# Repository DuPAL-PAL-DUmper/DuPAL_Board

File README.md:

# DuPAL board

## DISCLAIMER

Any use of this project is **under your own responsibility**.
You will be responsible of checking the correct construction and functionality of your board and the compatiblity of the chips You will insert into it.
By using this project You will agree that I cannot be held responsible if it will destroy any of your devices, damage your computer, burn down your house or whatever.

**Do NOT come to me for hand-holding** using this. It is NOT a plug-and-play tool, and it is something I created **for my own use** and I released in case someone might have an use for it.

## Introduction

The DuPAL boards are tools meant to help in dumping/reversing the content of some PLDs and memories.

The original DuPAL revision 2, currently supported by most tools, but limited in support to PAL devices (with the exclusion of PAL22) can be found [here](https://github.com/DuPAL-PAL-DUmper/DuPAL_Board/tree/master/board/DuPal_DIP).

The [DuPAL V3](https://github.com/DuPAL-PAL-DUmper/DuPAL_Board/tree/master/board/DuPal_V3), AKA "dupico", has more potential and will eventually support a much larger number of devices, but most of the tools have not yet been ported to it. Adapter pods for the dupico can be found [here](https://github.com/DuPAL-PAL-DUmper/DuPAL_Board/tree/master/board/dupico_pods).

### Sponsorship

This project is kindly sponsored by [PCBWay](https://pcbway.com).
PCBWay specializes in manufacturing high-quality PCBs and makes them affordable to hobbyist and professionals alike.

The range of services they offer include PCB prototyping, assembly, instant quotes for your order, a verification process by a team
of experts and an easy to use, hassle-free order process.

I'm grateful to PCBWay for the support in creating this project.

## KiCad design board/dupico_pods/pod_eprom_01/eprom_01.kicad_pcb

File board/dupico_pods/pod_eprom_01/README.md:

# EPROM_01 POD for dupico

## DISCLAIMER

Any use of this project is **under your own responsibility**.
You will be responsible of checking the correct construction and functionality of your board and the compatiblity of the chips You will insert into it.
By using this project You will agree that I cannot be held responsible if it will destroy any of your devices, damage your computer, burn down your house or whatever.

**Do NOT come to me for hand-holding** using this. It is NOT a plug-and-play tool, and it is something I created **for my own use** and I released in case someone might have an use for it.

## Introduction

The EPROM_01 POD is an adapter for the DuPAL V3 (AKA "dupico") meant to support the most common 24/28/32 pin ROMs, the only requirement being that they can be powered by 5V, have GND in the lower left pin and VCC in the upper right.

### Usage

This device is inserted in the ZIF socket of the dupico: if you installed a ZIF42 socket, it will fill all the 42 pins, if you installed a 48 pin socket, make sure to leave the bottom 6 pins empty (fit this in the topmost part of the socket).

When you fit a ROM device in it, make sure to align it to the bottom of the pod socket (so, a 28 pin device will leave empty the topmost 4 pins in the socket). 

Pin 32 on the pod socket is **hardwired to VCC**, there are other 7 selectable pins that can provide power, configured with 3 pins on the **ZIF42** socket:

| 24 | 23 | 22 | -> | Powered Pin (32 pin socket) |
| -- | -- | -- | -- | --------------------------- |
|  0 |  0 |  0 |    | 30 / 32                     |
|  0 |  0 |  1 |    | 28 / 32                     |
|  0 |  1 |  0 |    | 26 / 32                     |
|  0 |  1 |  1 |    | 25 / 32                     |
|  1 |  0 |  0 |    | 24 / 32                     |
|  1 |  0 |  1 |    | 23 / 32                     |
|  1 |  1 |  0 |    | 20 / 32                     |
|  1 |  1 |  1 |    | 32 only                     |

#### Socket connections

This drawing shows how the pin on the 32 socket are wired to the pins on the dupico's ZIF42.

```
            __ __
   1 ---> 1   U  32 <--- +5V (fixed)
   2 ---> 2      31 <-- 41
   3 ---> 3      30 <-- 40 --- Selectable +5V
   4 ---> 4      29 <-- 39
   5 ---> 5      28 <-- 38 --- Selectable +5V
   6 ---> 6      27 <-- 37
   7 ---> 7      26 <-- 36 --- Selectable +5V
   8 ---> 8      25 <-- 35 --- Selectable +5V
   9 ---> 9      24 <-- 34 --- Selectable +5V
  10 --> 10      23 <-- 33 --- Selectable +5V
  11 --> 11      22 <-- 32
  12 --->12      21 <-- 31
  13 --> 13      20 <-- 30 --- Selectable +5V
  14 --> 14      19 <-- 29
  15 --->15      18 <-- 28
GND ---> 16______17 <-- 27

```

## Hardware

The board was designed with [KiCad](https://kicad.org/) EDA.

In its current form, the board is relatively simple build, using through-hole and (non fine pitched) SMD components.

You can order the PCBs at [PCBWay](https://www.pcbway.com/project/shareproject/dupico_EPROM_01_POD_ed82b51c.html)!

### Bill of Materials

| Component         | Qty | Type / Value                   | Notes                                                                                            |
| ----------------- | --- | ------------------------------ | ------------------------------------------------------------------------------------------------ |
| J1                |  2  | 21 pin 2.54mm headers          | Use rounded pin headers to put less stress on dupico ZIF, snip the protruding part of the header |
| C1, C2            |  2  | 100nF / 1206 / ceramic         |                                                                                                  |
| Q1 - Q7           |  7  | MMBT3906                       |                                                                                                  |
| J2                |  1  | 32 pin wide socket             | Solder this AFTER the two J1 headers, you can use a ZIF32 socket.                                |
| U2                |  1  | 74ACT138 SOIC-16               |                                                                                                  |
| R1 - R7           |  7  | 1K / 1206                      |                                                                                                  |

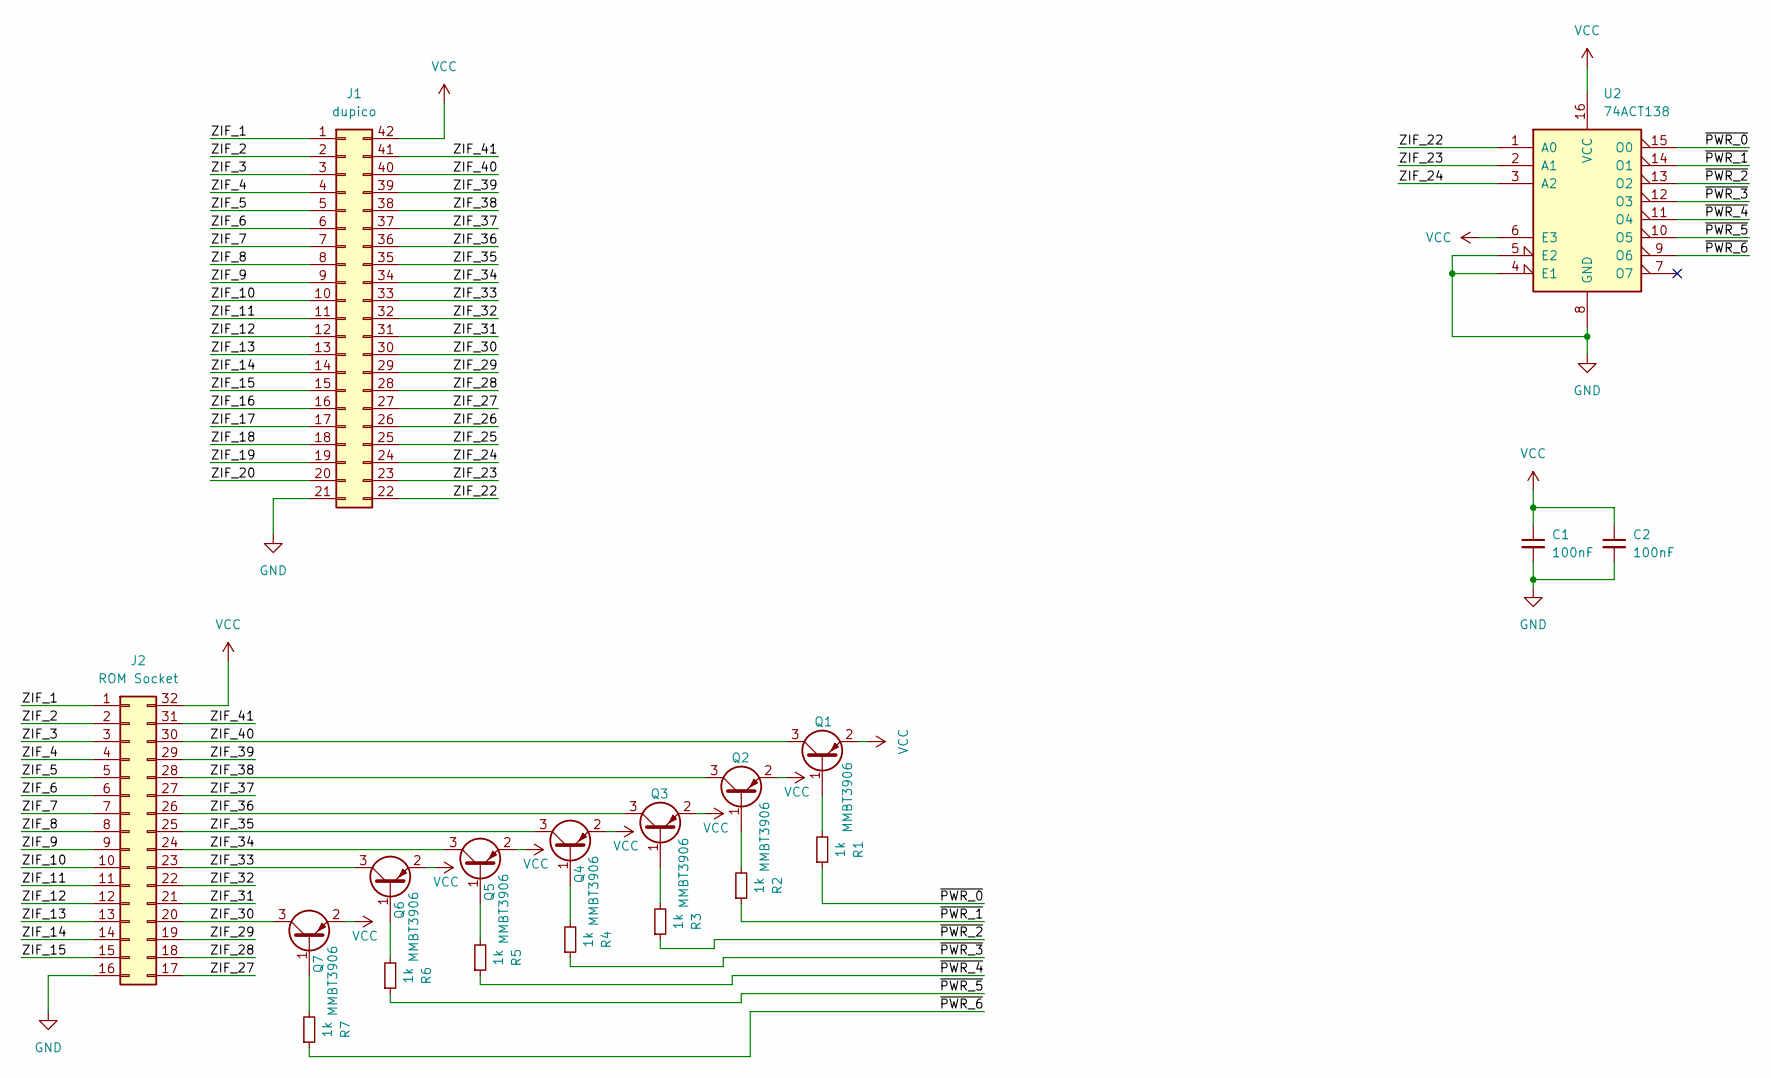
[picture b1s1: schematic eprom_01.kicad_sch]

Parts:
C1, C2: 100nF; C_1206_3216Metric_Pad1.33x1.80mm_HandSolder
J1: dupico; DIP-42_W15.24mm
J2: ROM Socket; DIP_Socket-32_W11.9_W12.7_W15.24_W17.78_W18.5_3M_232-1285-0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
Q1, Q2, Q3, Q4, Q5, Q6, Q7: MMBT3906; SOT-23
R1, R2, R3, R4, R5, R6, R7: 1k; R_1206_3216Metric_Pad1.30x1.75mm_HandSolder
U2: 74ACT138; SOIC-16_3.9x9.9mm_P1.27mm

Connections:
/ZIF_1: J1.1, J2.1
/ZIF_2: J1.2, J2.2
/ZIF_3: J1.3, J2.3
/ZIF_4: J1.4, J2.4
/ZIF_5: J1.5, J2.5
/ZIF_6: J1.6, J2.6
/ZIF_7: J1.7, J2.7
/ZIF_8: J1.8, J2.8
/ZIF_9: J1.9, J2.9
/ZIF_10: J1.10, J2.10
/ZIF_11: J1.11, J2.11
/ZIF_12: J1.12, J2.12
/ZIF_13: J1.13, J2.13
/ZIF_14: J1.14, J2.14
/ZIF_15: J1.15, J2.15
/ZIF_16: J1.16
/ZIF_17: J1.17
/ZIF_18: J1.18
/ZIF_19: J1.19
/ZIF_20: J1.20
/ZIF_22: J1.22, U2.1 (A0)
/ZIF_23: J1.23, U2.2 (A1)
/ZIF_24: J1.24, U2.3 (A2)
/ZIF_25: J1.25
/ZIF_26: J1.26
/ZIF_27: J1.27, J2.17
/ZIF_28: J1.28, J2.18
/ZIF_29: J1.29, J2.19
/ZIF_30: J1.30, J2.20, Q7.3 (C)
/ZIF_31: J1.31, J2.21
/ZIF_32: J1.32, J2.22
/ZIF_33: J1.33, J2.23, Q6.3 (C)
/ZIF_34: J1.34, J2.24, Q5.3 (C)
/ZIF_35: J1.35, J2.25, Q4.3 (C)
/ZIF_36: J1.36, J2.26, Q3.3 (C)
/ZIF_37: J1.37, J2.27
/ZIF_38: J1.38, J2.28, Q2.3 (C)
/ZIF_39: J1.39, J2.29
/ZIF_40: J1.40, J2.30, Q1.3 (C)
/ZIF_41: J1.41, J2.31
/~PWR_0: R1.1, U2.15 (O0)
/~PWR_1: R2.1, U2.14 (O1)
/~PWR_2: R3.1, U2.13 (O2)
/~PWR_3: R4.1, U2.12 (O3)
/~PWR_4: R5.1, U2.11 (O4)
/~PWR_5: R6.1, U2.10 (O5)
/~PWR_6: R7.1, U2.9 (O6)
GND: C1.2, C2.2, J1.21, J2.16, U2.4 (E1), U2.5 (E2), U2.8 (GND)
unnamed: Q1.1 (B), R1.2
unnamed: Q2.1 (B), R2.2
unnamed: Q3.1 (B), R3.2
unnamed: Q4.1 (B), R4.2
unnamed: Q5.1 (B), R5.2
unnamed: Q6.1 (B), R6.2
unnamed: Q7.1 (B), R7.2
VCC: C1.1, C2.1, J1.42, J2.32, Q1.2 (E), Q2.2 (E), Q3.2 (E), Q4.2 (E), Q5.2 (E), Q6.2 (E), Q7.2 (E), U2.6 (E3), U2.16 (VCC)

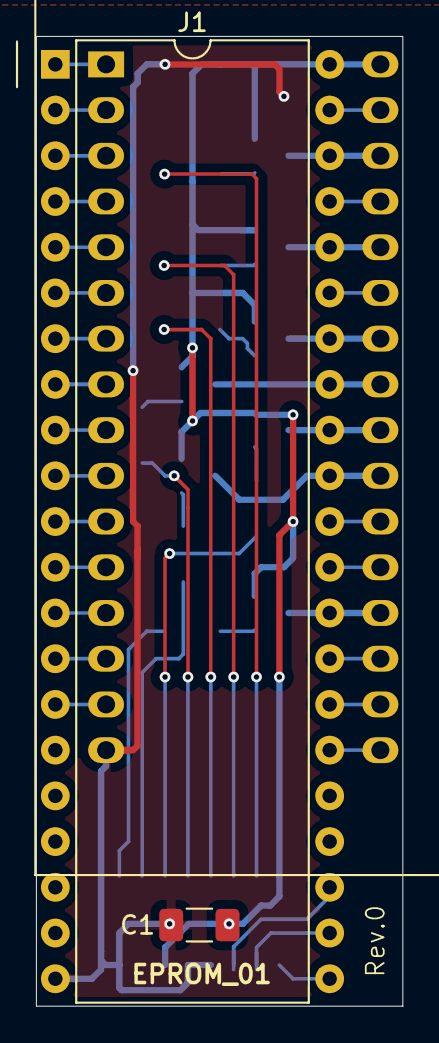
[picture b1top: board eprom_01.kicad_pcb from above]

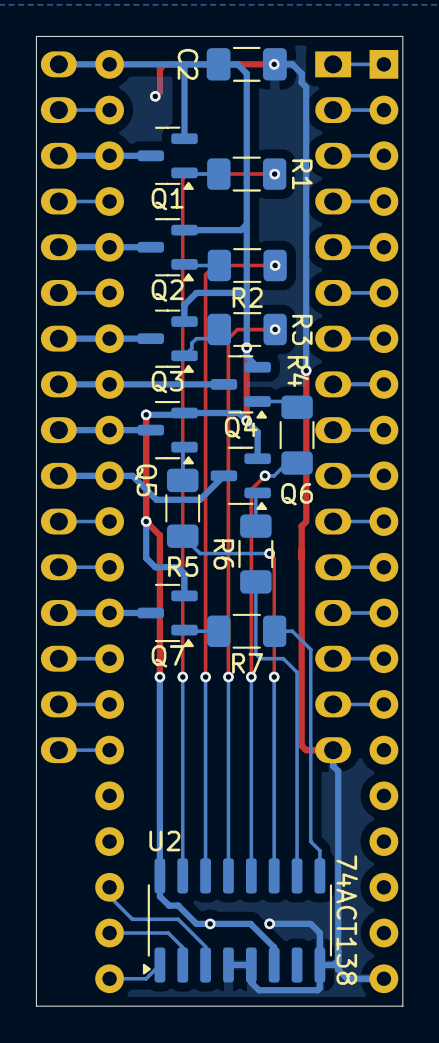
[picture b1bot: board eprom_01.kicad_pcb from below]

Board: 2 copper layers, 20.4 x 53.9 mm, 19 parts (16 on the bottom side), 49 nets.

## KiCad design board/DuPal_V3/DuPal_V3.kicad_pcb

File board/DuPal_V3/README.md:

# DuPAL V3 "dupico" board

## DISCLAIMER

Any use of this project is **under your own responsibility**.
You will be responsible of checking the correct construction and functionality of your board and the compatiblity of the chips You will insert into it.
By using this project You will agree that I cannot be held responsible if it will destroy any of your devices, damage your computer, burn down your house or whatever.

**Do NOT come to me for hand-holding** using this. It is NOT a plug-and-play tool, and it is something I created **for my own use** and I released in case someone might have an use for it.

## Introduction

The DuPAL V3, AKA "dupico" board is a simple circuit that mounts a Raspberry Pico (RP2040), 74HC595 SIPO registers, 74HCT166 PISO registers, and some glue logic and passives.

The board is designed to help me analyze and dump various types of PLDs and memories.

Various adapters (or "pods") can be designed to suit different types of ICs. The pods will be plugged in the ZIF42 socket.

## Software

### Firmware

See [here](https://github.com/DuPAL-PAL-DUmper/dupico_firmware) for details.

### dpdumper

This is a generic dumper for combinatorial ICs. See [here](https://github.com/DuPAL-PAL-DUmper/dpdumper) for the repository.

## Hardware

The board was designed with [KiCad](https://kicad.org/) EDA.

In its current form, the board is relatively simple build, using through-hole and (non fine pitched) SMD components.

### Bill of Materials

| Component         | Qty | Type / Value                   | Notes                                                    |
| ----------------- | --- | ------------------------------ | -------------------------------------------------------- |
| C1, C3 - C14      | 13  | 100nF / 1206 / ceramic         |                                                          |
| C2                |  1  | 10uF / 10V / 1206 / ceramic    |                                                          |
| D1                |  1  | 1N5818                         |                                                          |
| D2, D3, D4        |  3  | Your choice of 1206 SMD LEDs   |                                                          |
| F1                |  1  | 1206 500mA fuse                | https://www.mouser.it/ProductDetail/530-C1F500           |
| J1                |  1  | ZIF42 or ZIF48 socket, wide    | If using ZIF42, leave the bottom 6 pins empty on the PCB |
| J2                |  1  | 1x3 header, 2.54mm pitch       |                                                          |
| J3                |  1  | 2x8 header, 2.54mm pitch       |                                                          |
| J4, J5            |  2  | 1x21 header, 2.54mm pitch      |                                                          |
| K1                |  1  | Omron G6K-2P-Y-DC5             | https://www.mouser.it/ProductDetail/653-G6K-2P-Y-DC5     |
| Q1                |  1  | 2N3904                         |                                                          |
| R1                |  1  | 2.2K / 1206                    |                                                          |
| R2 - R41, R86     | 41  | 10K / 1206                     |                                                          |
| R42, R46 - R85    | 41  | 470K / 1206                    |                                                          |
| R43 - R45         |  3  | 1.2K / 1206                    |                                                          |
| SW1               |  1  | Switch button 6mm              |                                                          |
| U1                |  1  | Pi Pico                        |                                                          |
| U2 - U6           |  5  | 74HCT595 SOIC-16               | HCT variant is important                                 |
| U7                |  1  | 74HCT02 SOIC-14                | HCT variant is important                                 |
| U8 - U12          |  5  | 74HCT166 SOIC-16               | HCT variant is important                                 |
| U13               |  1  | SN74LV1T125DBV SOT-23-5        | https://www.mouser.it/ProductDetail/595-74LV1T125DBVRG4  |

⚠️**WARNING:**⚠️ Note that U10, on the backside of the PCB, has the opposite orientation in respect to U8, U9, U11 and U12. This is NOT a mistake, trust the silkscreen in this case.

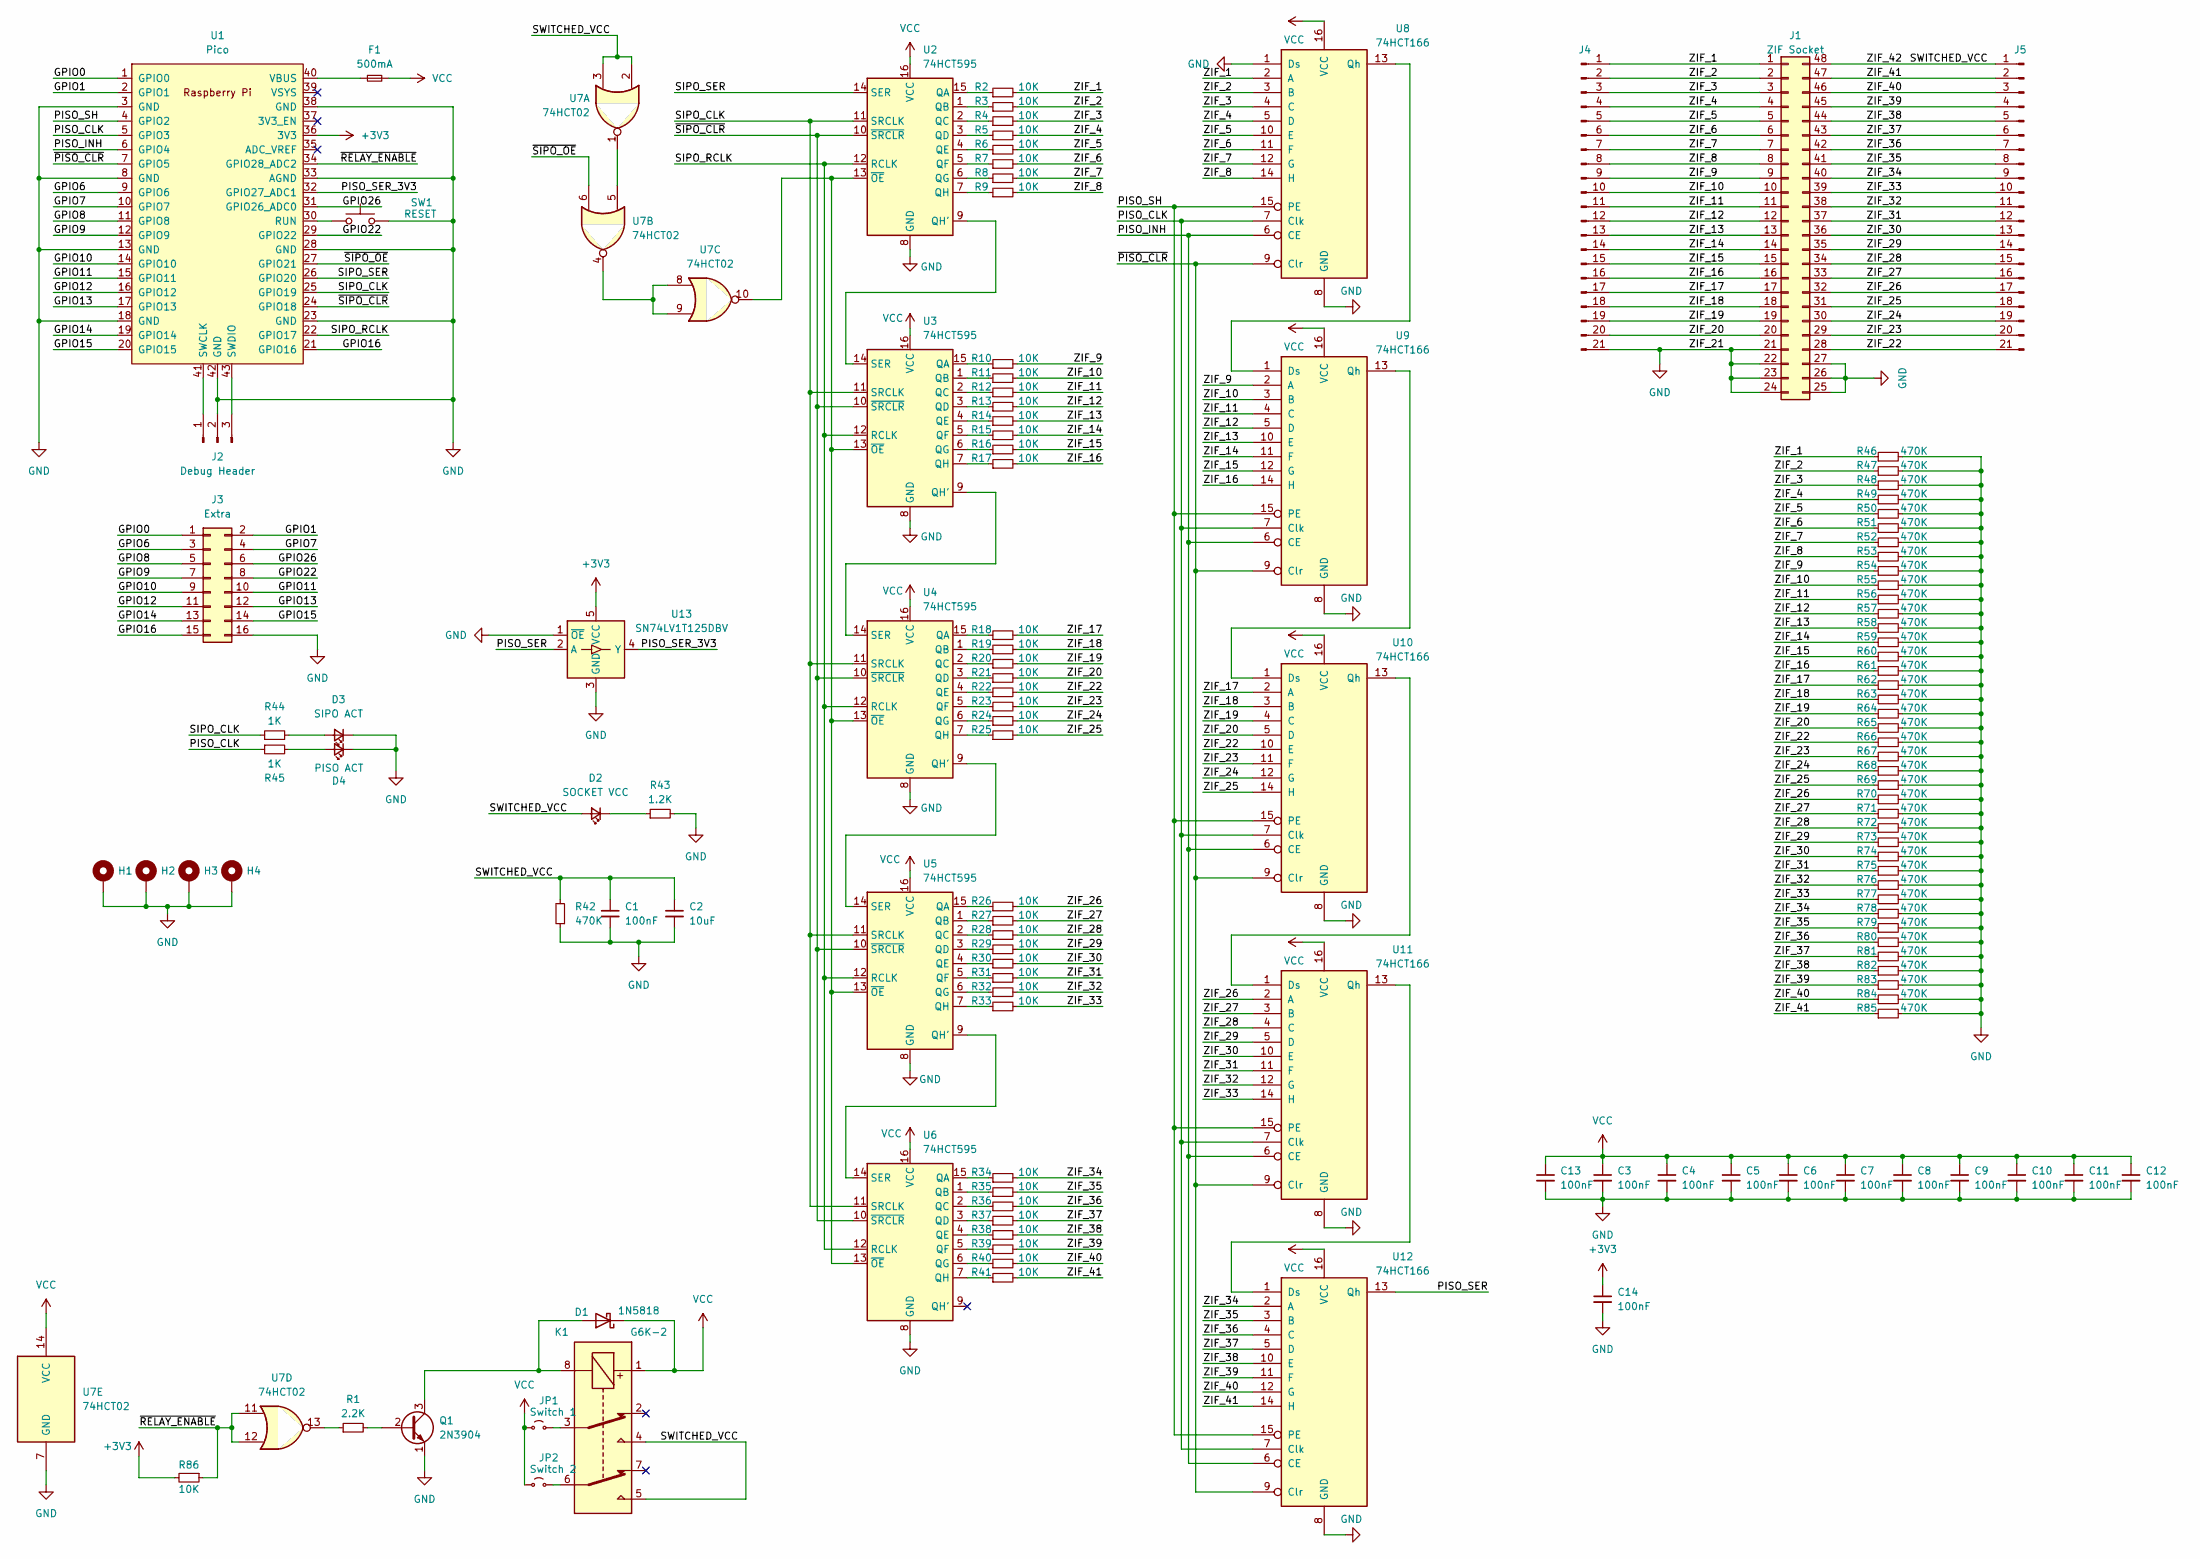
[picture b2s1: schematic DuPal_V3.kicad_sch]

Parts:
C1, C3, C4, C5, C6, C7, C8, C9, C10, C11, C12, C13, C14: 100nF; C_1206_3216Metric_Pad1.33x1.80mm_HandSolder
C2: 10uF; C_1206_3216Metric_Pad1.33x1.80mm_HandSolder
D1: 1N5818; D_DO-41_SOD81_P10.16mm_Horizontal
D2: SOCKET VCC; LED_1206_3216Metric_Pad1.42x1.75mm_HandSolder
D3: SIPO ACT; LED_1206_3216Metric_Pad1.42x1.75mm_HandSolder
D4: PISO ACT; LED_1206_3216Metric_Pad1.42x1.75mm_HandSolder
F1: 500mA; Fuse_1206_3216Metric_Pad1.42x1.75mm_HandSolder
H1, H2, H3, H4: MountingHole_Pad; MountingHole_3.2mm_M3_DIN965_Pad
J1: ZIF Socket; DIP_Socket-48
J2: Debug Header; PinHeader_1x03_P2.54mm_Vertical
J3: Extra; PinHeader_2x08_P2.54mm_Vertical
J4, J5: Conn_01x21_Pin; PinHeader_1x21_P2.54mm_Vertical
JP1: Switch 1; SolderJumper-2_P1.3mm_Bridged_RoundedPad1.0x1.5mm
JP2: Switch 2; SolderJumper-2_P1.3mm_Open_RoundedPad1.0x1.5mm
K1: G6K-2; Relay_DPDT_Omron_G6K-2P-Y
Q1: 2N3904; TO-92_Inline
R1: 2.2K; R_1206_3216Metric_Pad1.30x1.75mm_HandSolder
R2, R3, R4, R5, R6, R7, R8, R9, R10, R11, R12, R13, R14, R15, R16, R17, R18, R19, R20, R21, R22, R23, R24, R25, R26, R27, R28, R29, R30, R31, R32, R33, R34, R35, R36, R37, R38, R39, R40, R41, R86: 10K; R_1206_3216Metric_Pad1.30x1.75mm_HandSolder
R42, R46, R47, R48, R49, R50, R51, R52, R53, R54, R55, R56, R57, R58, R59, R60, R61, R62, R63, R64, R65, R66, R67, R68, R69, R70, R71, R72, R73, R74, R75, R76, R77, R78, R79, R80, R81, R82, R83, R84, R85: 470K; R_1206_3216Metric_Pad1.30x1.75mm_HandSolder
R43: 1.2K; R_1206_3216Metric_Pad1.30x1.75mm_HandSolder
R44, R45: 1K; R_1206_3216Metric_Pad1.30x1.75mm_HandSolder
SW1: RESET; SW_PUSH_6mm
U1: Pico; RPi_Pico_SMD_TH
U2, U3, U4, U5, U6: 74HCT595; SOIC-16_3.9x9.9mm_P1.27mm
U7: 74HCT02; SOIC-14_3.9x8.7mm_P1.27mm
U8, U9, U10, U11, U12: 74HCT166; SOIC-16_3.9x9.9mm_P1.27mm
U13: SN74LV1T125DBV; SOT-23-5

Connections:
+3V3: C14.1, R86.2, U1.36 (3V3), U13.5 (VCC)
/GPIO0: J3.1, U1.1 (GPIO0)
/GPIO1: J3.2, U1.2 (GPIO1)
/GPIO6: J3.3, U1.9 (GPIO6)
/GPIO7: J3.4, U1.10 (GPIO7)
/GPIO8: J3.5, U1.11 (GPIO8)
/GPIO9: J3.7, U1.12 (GPIO9)
/GPIO10: J3.9, U1.14 (GPIO10)
/GPIO11: J3.10, U1.15 (GPIO11)
/GPIO12: J3.11, U1.16 (GPIO12)
/GPIO13: J3.12, U1.17 (GPIO13)
/GPIO14: J3.13, U1.19 (GPIO14)
/GPIO15: J3.14, U1.20 (GPIO15)
/GPIO16: J3.15, U1.21 (GPIO16)
/GPIO22: J3.8, U1.29 (GPIO22)
/GPIO26: J3.6, U1.31 (GPIO26_ADC0)
/PISO_CLK: R45.1, U1.5 (GPIO3), U8.7 (Clk), U9.7 (Clk), U10.7 (Clk), U11.7 (Clk), U12.7 (Clk)
/PISO_INH: U1.6 (GPIO4), U8.6 (CE), U9.6 (CE), U10.6 (CE), U11.6 (CE), U12.6 (CE)
/PISO_SER: U12.13 (Qh), U13.2 (A)
/PISO_SER_3V3: U1.32 (GPIO27_ADC1), U13.4 (Y)
/PISO_SH: U1.4 (GPIO2), U8.15 (PE), U9.15 (PE), U10.15 (PE), U11.15 (PE), U12.15 (PE)
/SIPO_CLK: R44.1, U1.25 (GPIO19), U2.11 (SRCLK), U3.11 (SRCLK), U4.11 (SRCLK), U5.11 (SRCLK), U6.11 (SRCLK)
/SIPO_RCLK: U1.22 (GPIO17), U2.12 (RCLK), U3.12 (RCLK), U4.12 (RCLK), U5.12 (RCLK), U6.12 (RCLK)
/SIPO_SER: U1.26 (GPIO20), U2.14 (SER)
/SWITCHED_VCC: C1.1, C2.1, D2.2 (A), J1.48, J5.1, K1.4, K1.5, R42.2, U7.2, U7.3
/ZIF_1: J1.1, J4.1, R2.2, R46.1, U8.2 (A)
/ZIF_2: J1.2, J4.2, R3.2, R47.1, U8.3 (B)
/ZIF_3: J1.3, J4.3, R4.2, R48.1, U8.4 (C)
/ZIF_4: J1.4, J4.4, R5.2, R49.1, U8.5 (D)
/ZIF_5: J1.5, J4.5, R6.2, R50.1, U8.10 (E)
/ZIF_6: J1.6, J4.6, R7.2, R51.1, U8.11 (F)
/ZIF_7: J1.7, J4.7, R8.2, R52.1, U8.12 (G)
/ZIF_8: J1.8, J4.8, R9.2, R53.1, U8.14 (H)
/ZIF_9: J1.9, J4.9, R10.2, R54.1, U9.2 (A)
/ZIF_10: J1.10, J4.10, R11.2, R55.1, U9.3 (B)
/ZIF_11: J1.11, J4.11, R12.2, R56.1, U9.4 (C)
/ZIF_12: J1.12, J4.12, R13.2, R57.1, U9.5 (D)
/ZIF_13: J1.13, J4.13, R14.2, R58.1, U9.10 (E)
/ZIF_14: J1.14, J4.14, R15.2, R59.1, U9.11 (F)
/ZIF_15: J1.15, J4.15, R16.2, R60.1, U9.12 (G)
/ZIF_16: J1.16, J4.16, R17.2, R61.1, U9.14 (H)
/ZIF_17: J1.17, J4.17, R18.2, R62.1, U10.2 (A)
/ZIF_18: J1.18, J4.18, R19.2, R63.1, U10.3 (B)
/ZIF_19: J1.19, J4.19, R20.2, R64.1, U10.4 (C)
/ZIF_20: J1.20, J4.20, R21.2, R65.1, U10.5 (D)
/ZIF_22: J1.28, J5.21, R22.2, R66.1, U10.10 (E)
/ZIF_23: J1.29, J5.20, R23.2, R67.1, U10.11 (F)
/ZIF_24: J1.30, J5.19, R24.2, R68.1, U10.12 (G)
/ZIF_25: J1.31, J5.18, R25.2, R69.1, U10.14 (H)
/ZIF_26: J1.32, J5.17, R26.2, R70.1, U11.2 (A)
/ZIF_27: J1.33, J5.16, R27.2, R71.1, U11.3 (B)
/ZIF_28: J1.34, J5.15, R28.2, R72.1, U11.4 (C)
/ZIF_29: J1.35, J5.14, R29.2, R73.1, U11.5 (D)
/ZIF_30: J1.36, J5.13, R30.2, R74.1, U11.10 (E)
/ZIF_31: J1.37, J5.12, R31.2, R75.1, U11.11 (F)
/ZIF_32: J1.38, J5.11, R32.2, R76.1, U11.12 (G)
/ZIF_33: J1.39, J5.10, R33.2, R77.1, U11.14 (H)
/ZIF_34: J1.40, J5.9, R34.2, R78.1, U12.2 (A)
/ZIF_35: J1.41, J5.8, R35.2, R79.1, U12.3 (B)
/ZIF_36: J1.42, J5.7, R36.2, R80.1, U12.4 (C)
/ZIF_37: J1.43, J5.6, R37.2, R81.1, U12.5 (D)
/ZIF_38: J1.44, J5.5, R38.2, R82.1, U12.10 (E)
/ZIF_39: J1.45, J5.4, R39.2, R83.1, U12.11 (F)
/ZIF_40: J1.46, J5.3, R40.2, R84.1, U12.12 (G)
/ZIF_41: J1.47, J5.2, R41.2, R85.1, U12.14 (H)
/~PISO_CLR: U1.7 (GPIO5), U8.9 (Clr), U9.9 (Clr), U10.9 (Clr), U11.9 (Clr), U12.9 (Clr)
/~RELAY_ENABLE: R86.1, U1.34 (GPIO28_ADC2), U7.11, U7.12
/~SIPO_CLR: U1.24 (GPIO18), U2.10 (~SRCLR), U3.10 (~SRCLR), U4.10 (~SRCLR), U5.10 (~SRCLR), U6.10 (~SRCLR)
/~SIPO_OE: U1.27 (GPIO21), U7.6
GND: C1.2, C2.2, C3.2, C4.2, C5.2, C6.2, C7.2, C8.2, C9.2, C10.2, C11.2, C12.2, C13.2, C14.2, D3.1 (K), D4.1 (K), H1.1, H2.1, H3.1, H4.1, J1.21, J1.22, J1.23, J1.24, J1.25, J1.26, J1.27, J2.2, J3.16, J4.21, Q1.1 (E), R42.1, R43.2, R46.2, R47.2, R48.2, R49.2, R50.2, R51.2, R52.2, R53.2, R54.2, R55.2, R56.2, R57.2, R58.2, R59.2, R60.2, R61.2, R62.2, R63.2, R64.2, R65.2, R66.2, R67.2, R68.2, R69.2, R70.2, R71.2, R72.2, R73.2, R74.2, R75.2, R76.2, R77.2, R78.2, R79.2, R80.2, R81.2, R82.2, R83.2, R84.2, R85.2, SW1.2, U1.3 (GND), U1.8 (GND), U1.13 (GND), U1.18 (GND), U1.23 (GND), U1.28 (GND), U1.33 (AGND), U1.38 (GND), U1.42 (GND), U2.8 (GND), U3.8 (GND), U4.8 (GND), U5.8 (GND), U6.8 (GND), U7.7 (GND), U8.1 (Ds), U8.8 (GND), U9.8 (GND), U10.8 (GND), U11.8 (GND), U12.8 (GND), U13.1 (~OE), U13.3 (GND)
unnamed: D1.2 (A), K1.8, Q1.3 (C)
unnamed: D2.1 (K), R43.1
unnamed: D3.2 (A), R44.2
unnamed: D4.2 (A), R45.2
unnamed: J2.1, U1.41 (SWCLK)
unnamed: J2.3, U1.43 (SWDIO)
unnamed: JP1.2 (B), K1.3
unnamed: JP2.2 (B), K1.6
unnamed: Q1.2 (B), R1.2
unnamed: R1.1, U7.13
unnamed: SW1.1, U1.30 (RUN)
unnamed: F1.1, U1.40 (VBUS)
unnamed: R2.1, U2.15 (QA)
unnamed: R3.1, U2.1 (QB)
unnamed: R4.1, U2.2 (QC)
unnamed: R5.1, U2.3 (QD)
unnamed: R6.1, U2.4 (QE)
unnamed: R7.1, U2.5 (QF)
unnamed: R8.1, U2.6 (QG)
unnamed: U2.9 (QH'), U3.14 (SER)
unnamed: R9.1, U2.7 (QH)
unnamed: U2.13 (~OE), U3.13 (~OE), U4.13 (~OE), U5.13 (~OE), U6.13 (~OE), U7.10
unnamed: R10.1, U3.15 (QA)
unnamed: R11.1, U3.1 (QB)
unnamed: R12.1, U3.2 (QC)
unnamed: R13.1, U3.3 (QD)
unnamed: R14.1, U3.4 (QE)
unnamed: R15.1, U3.5 (QF)
unnamed: R16.1, U3.6 (QG)
unnamed: U3.9 (QH'), U4.14 (SER)
unnamed: R17.1, U3.7 (QH)
unnamed: R18.1, U4.15 (QA)
unnamed: R19.1, U4.1 (QB)
unnamed: R20.1, U4.2 (QC)
unnamed: R21.1, U4.3 (QD)
unnamed: R22.1, U4.4 (QE)
unnamed: R23.1, U4.5 (QF)
unnamed: R24.1, U4.6 (QG)
unnamed: U4.9 (QH'), U5.14 (SER)
unnamed: R25.1, U4.7 (QH)
unnamed: R26.1, U5.15 (QA)
unnamed: R27.1, U5.1 (QB)
unnamed: R28.1, U5.2 (QC)
unnamed: R29.1, U5.3 (QD)
unnamed: R30.1, U5.4 (QE)
unnamed: R31.1, U5.5 (QF)
unnamed: R32.1, U5.6 (QG)
unnamed: U5.9 (QH'), U6.14 (SER)
unnamed: R33.1, U5.7 (QH)
unnamed: R34.1, U6.15 (QA)
unnamed: R35.1, U6.1 (QB)
unnamed: R36.1, U6.2 (QC)
unnamed: R37.1, U6.3 (QD)
unnamed: R38.1, U6.4 (QE)
unnamed: R39.1, U6.5 (QF)
unnamed: R40.1, U6.6 (QG)
unnamed: R41.1, U6.7 (QH)
unnamed: U7.1, U7.5
unnamed: U7.4, U7.8, U7.9
unnamed: U8.13 (Qh), U9.1 (Ds)
unnamed: U9.13 (Qh), U10.1 (Ds)
unnamed: U10.13 (Qh), U11.1 (Ds)
unnamed: U11.13 (Qh), U12.1 (Ds)
VCC: C3.1, C4.1, C5.1, C6.1, C7.1, C8.1, C9.1, C10.1, C11.1, C12.1, C13.1, D1.1 (K), F1.2, JP1.1 (A), JP2.1 (A), K1.1, U2.16 (VCC), U3.16 (VCC), U4.16 (VCC), U5.16 (VCC), U6.16 (VCC), U7.14 (VCC), U8.16 (VCC), U9.16 (VCC), U10.16 (VCC), U11.16 (VCC), U12.16 (VCC)

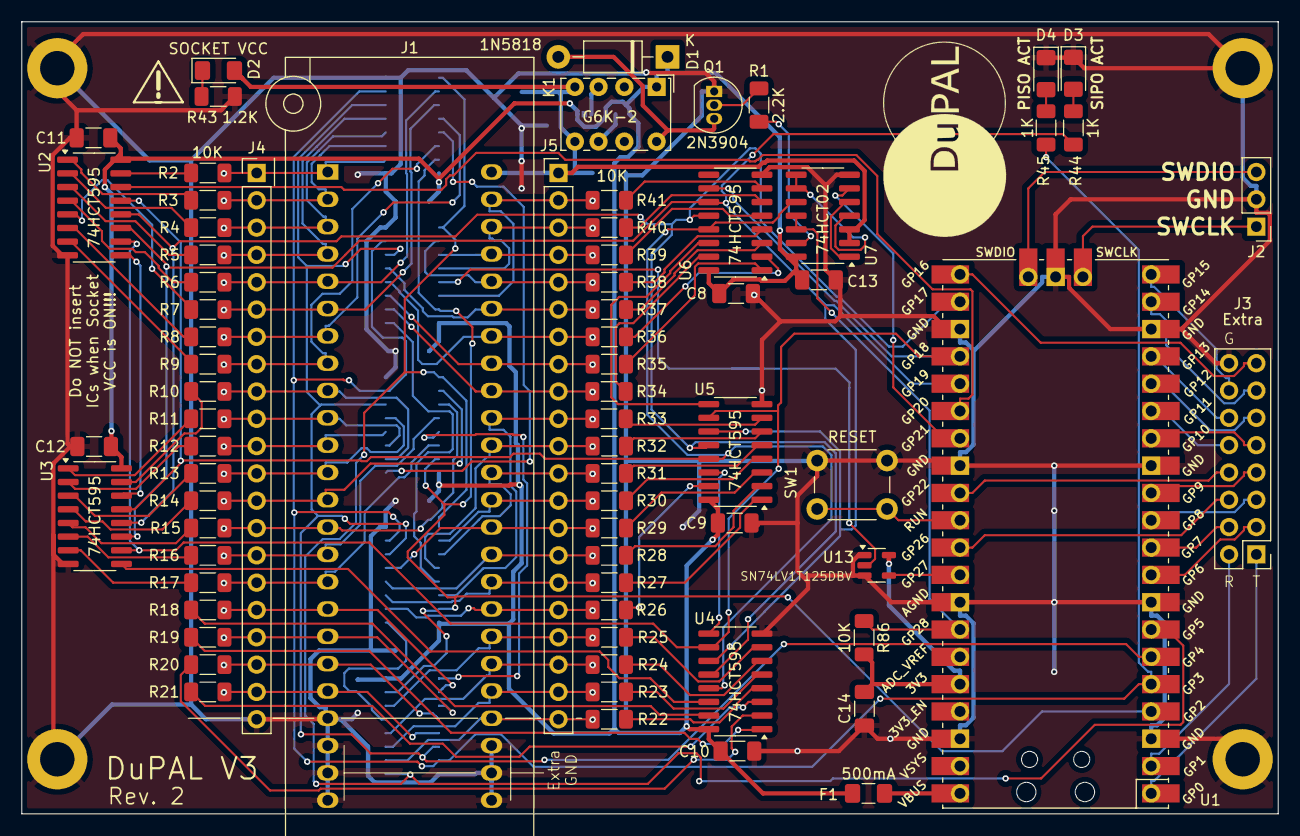
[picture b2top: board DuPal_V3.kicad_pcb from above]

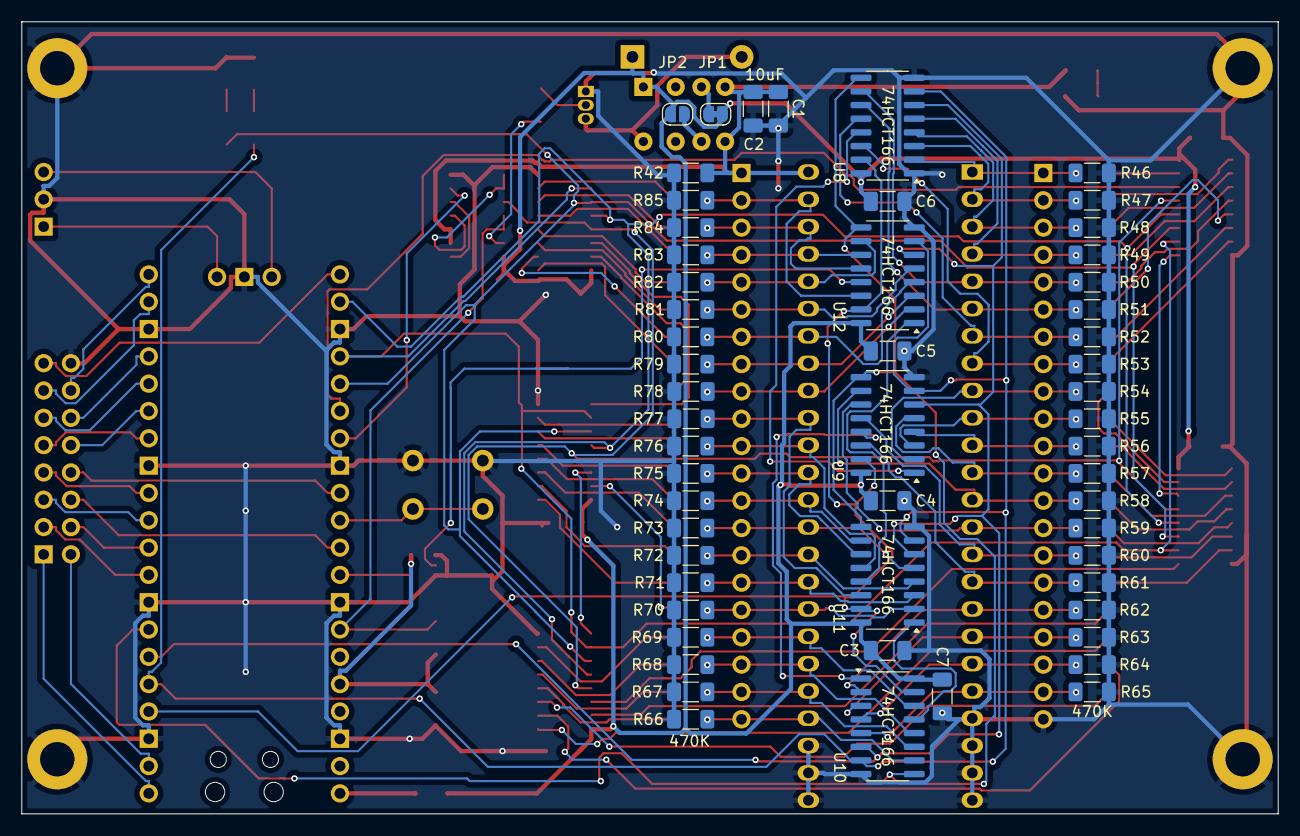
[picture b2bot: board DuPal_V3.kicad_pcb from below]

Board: 2 copper layers, 116.8 x 73.7 mm, 132 parts (55 on the bottom side), 134 nets.

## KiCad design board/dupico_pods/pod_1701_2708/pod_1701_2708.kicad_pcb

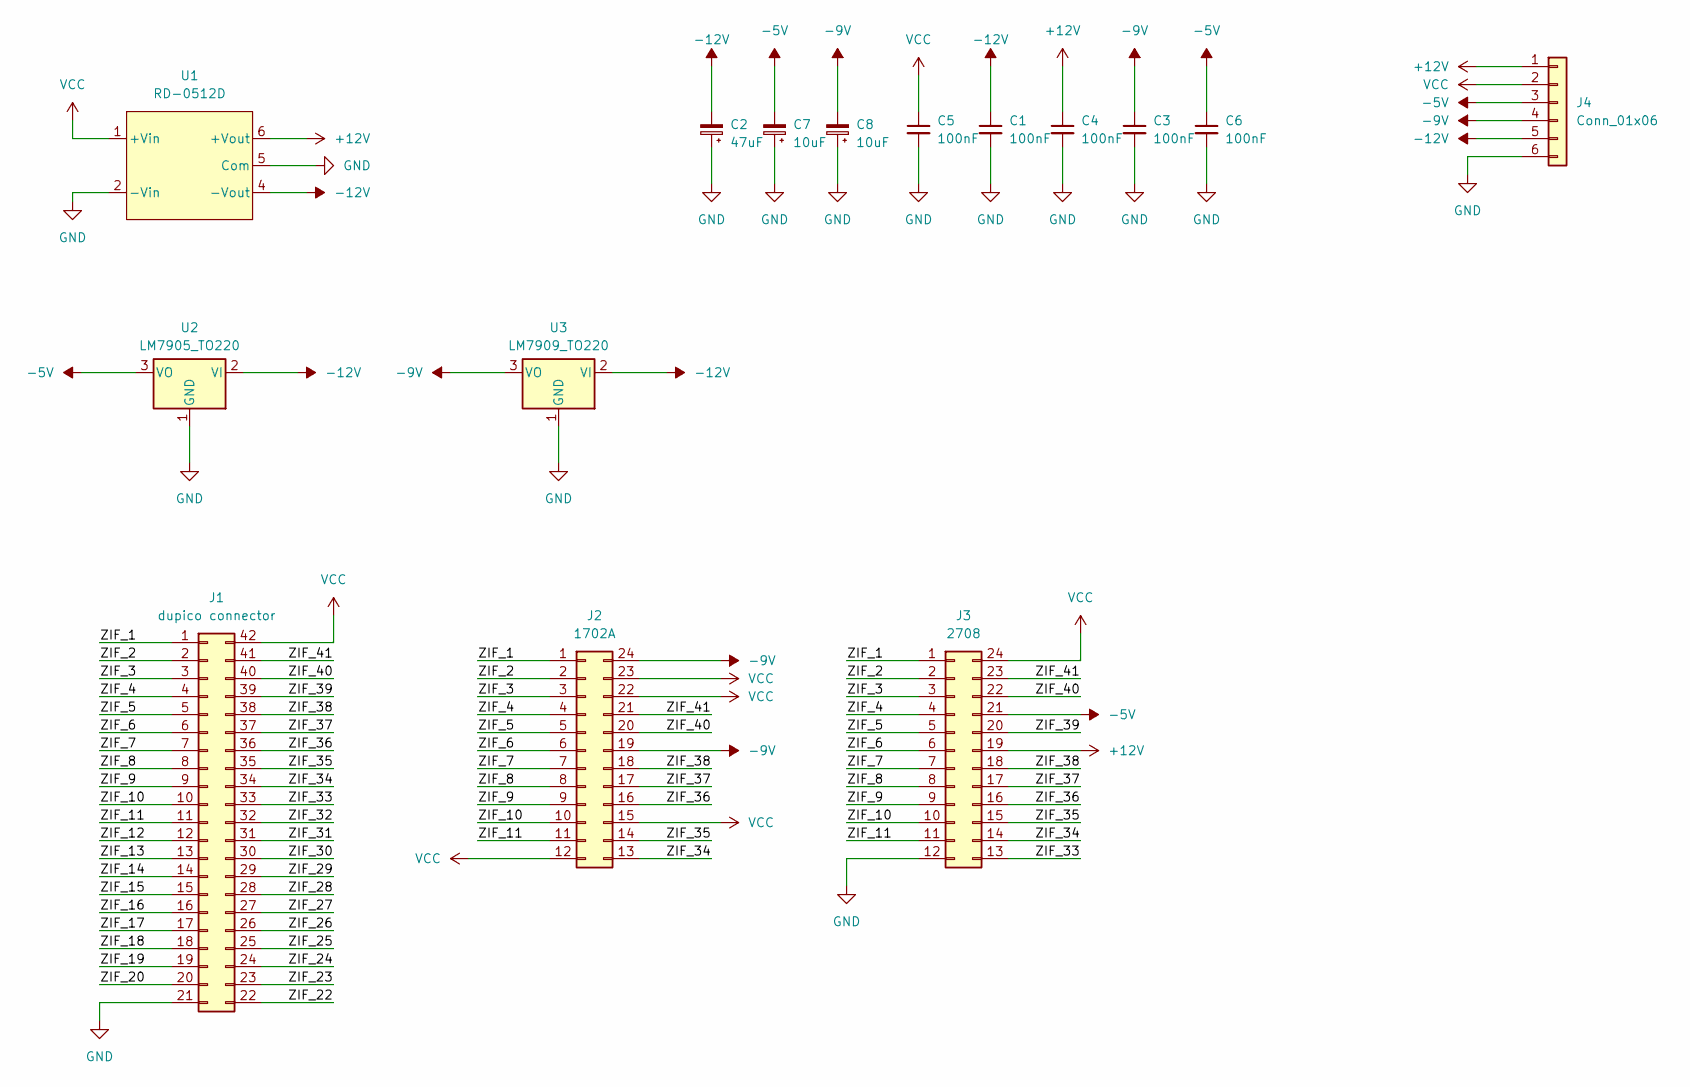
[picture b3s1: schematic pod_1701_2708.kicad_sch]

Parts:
C1, C3, C4, C5, C6: 100nF; C_1206_3216Metric_Pad1.33x1.80mm_HandSolder
C2: 47uF; CP_Radial_D5.0mm_P2.00mm
C7, C8: 10uF; CP_Radial_D5.0mm_P2.00mm
J1: dupico connector; DIP-42_W15.24mm
J2: 1702A; DIP_Socket-24_W11.9_W12.7_W15.24_W17.78_W18.5_3M_224-1275-0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
J3: 2708; DIP_Socket-24_W11.9_W12.7_W15.24_W17.78_W18.5_3M_224-1275-0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
J4: Conn_01x06; PinHeader_1x06_P2.54mm_Vertical
U1: RD-0512D; Recom_SIP6
U2: LM7905_TO220; TO-220-3_Vertical
U3: LM7909_TO220; TO-220-3_Vertical

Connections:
+12V: C4.1, J3.19, J4.1, U1.6 (+Vout)
-5V: C6.1, C7.2, J3.21, J4.3, U2.3 (VO)
-9V: C3.1, C8.2, J2.19, J2.24, J4.4, U3.3 (VO)
-12V: C1.1, C2.2, J4.5, U1.4 (-Vout), U2.2 (VI), U3.2 (VI)
/ZIF_1: J1.1, J2.1, J3.1
/ZIF_2: J1.2, J2.2, J3.2
/ZIF_3: J1.3, J2.3, J3.3
/ZIF_4: J1.4, J2.4, J3.4
/ZIF_5: J1.5, J2.5, J3.5
/ZIF_6: J1.6, J2.6, J3.6
/ZIF_7: J1.7, J2.7, J3.7
/ZIF_8: J1.8, J2.8, J3.8
/ZIF_9: J1.9, J2.9, J3.9
/ZIF_10: J1.10, J2.10, J3.10
/ZIF_11: J1.11, J2.11, J3.11
/ZIF_12: J1.12
/ZIF_13: J1.13
/ZIF_14: J1.14
/ZIF_15: J1.15
/ZIF_16: J1.16
/ZIF_17: J1.17
/ZIF_18: J1.18
/ZIF_19: J1.19
/ZIF_20: J1.20
/ZIF_22: J1.22
/ZIF_23: J1.23
/ZIF_24: J1.24
/ZIF_25: J1.25
/ZIF_26: J1.26
/ZIF_27: J1.27
/ZIF_28: J1.28
/ZIF_29: J1.29
/ZIF_30: J1.30
/ZIF_31: J1.31
/ZIF_32: J1.32
/ZIF_33: J1.33, J3.13
/ZIF_34: J1.34, J2.13, J3.14
/ZIF_35: J1.35, J2.14, J3.15
/ZIF_36: J1.36, J2.16, J3.16
/ZIF_37: J1.37, J2.17, J3.17
/ZIF_38: J1.38, J2.18, J3.18
/ZIF_39: J1.39, J3.20
/ZIF_40: J1.40, J2.20, J3.22
/ZIF_41: J1.41, J2.21, J3.23
GND: C1.2, C2.1, C3.2, C4.2, C5.2, C6.2, C7.1, C8.1, J1.21, J3.12, J4.6, U1.2 (-Vin), U1.5 (Com), U2.1 (GND), U3.1 (GND)
VCC: C5.1, J1.42, J2.12, J2.15, J2.22, J2.23, J3.24, J4.2, U1.1 (+Vin)

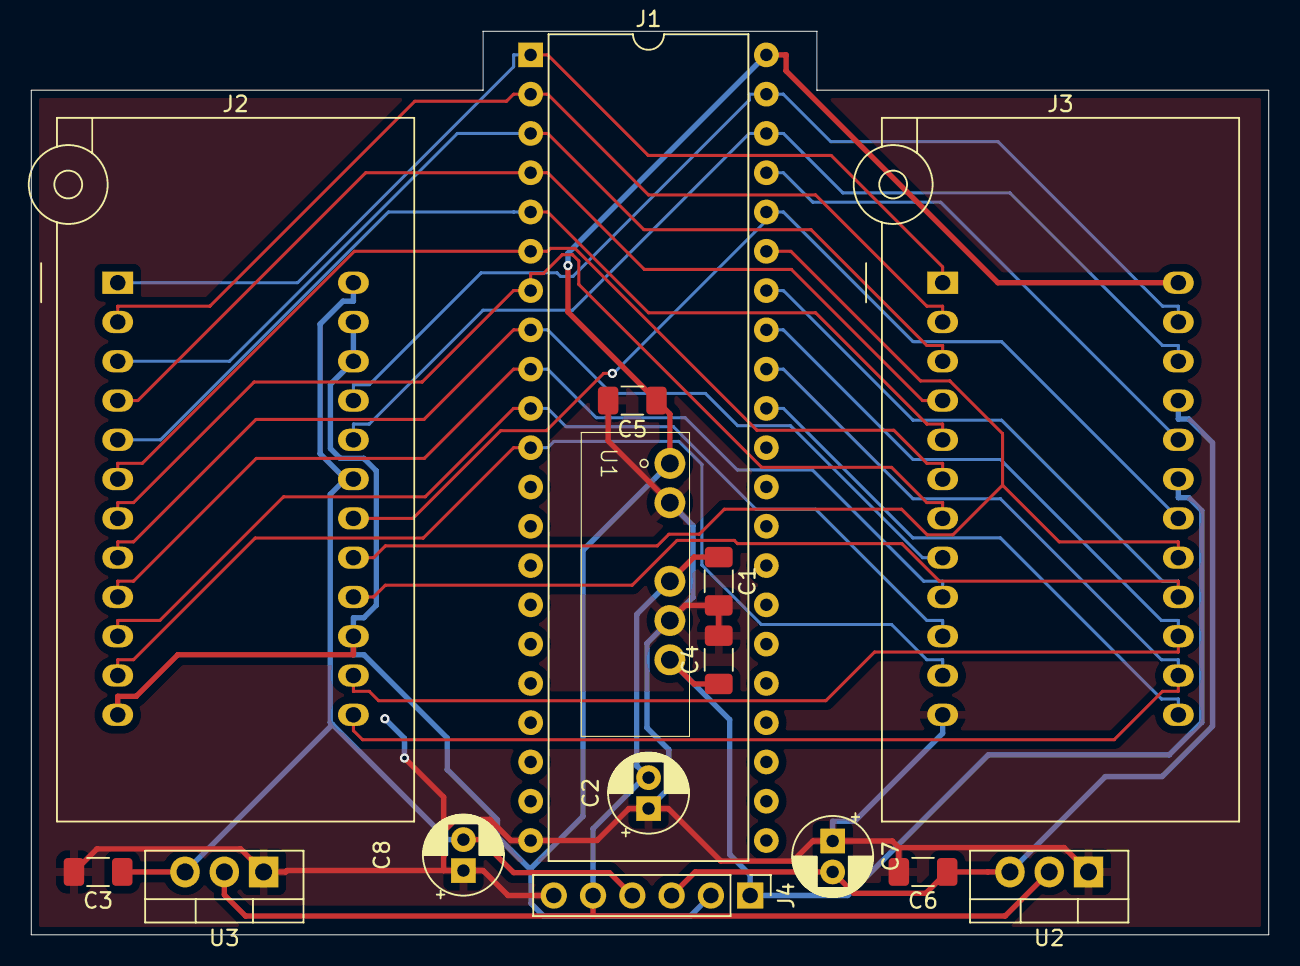
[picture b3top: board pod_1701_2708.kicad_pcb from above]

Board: 2 copper layers, 80.0 x 58.4 mm, 15 parts (0 on the bottom side), 26 nets.

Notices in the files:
board/DuPal_DIP/DuPal_DIP.kicad_pcb:
CC-BY-SA-4.0
